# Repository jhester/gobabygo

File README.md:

GoBabyGo Project Repository
=====

This repo holds the firmware, software, hardware, and other files fort the GoBabyGo utilization project.

#### Visualize Data with Google Earth

Use the `create_nmea.py` script in the `analysis` folder to convert gathered GPS data into a single [NMEA file](https://www.gpsworld.com/what-exactly-is-gps-nmea-data/) which can be dragged into [Google Earth Pro (free)](https://www.google.com/earth/versions/#earth-pro), the desktop app.

To do this you need Python, once installed run the following in a command prompt or in a terminal where you specify the path to all the data and then specify the name of the NMEA file:

```
python create_nmea.py folder/where/files/are -o outputfile.nmea
```

If you import only tracks, it renders faster  but you dont get each value. If you import the LineStrings then it shows every value and also shows direction and time which is nice.

This could be trimmed down to show per day possibly.

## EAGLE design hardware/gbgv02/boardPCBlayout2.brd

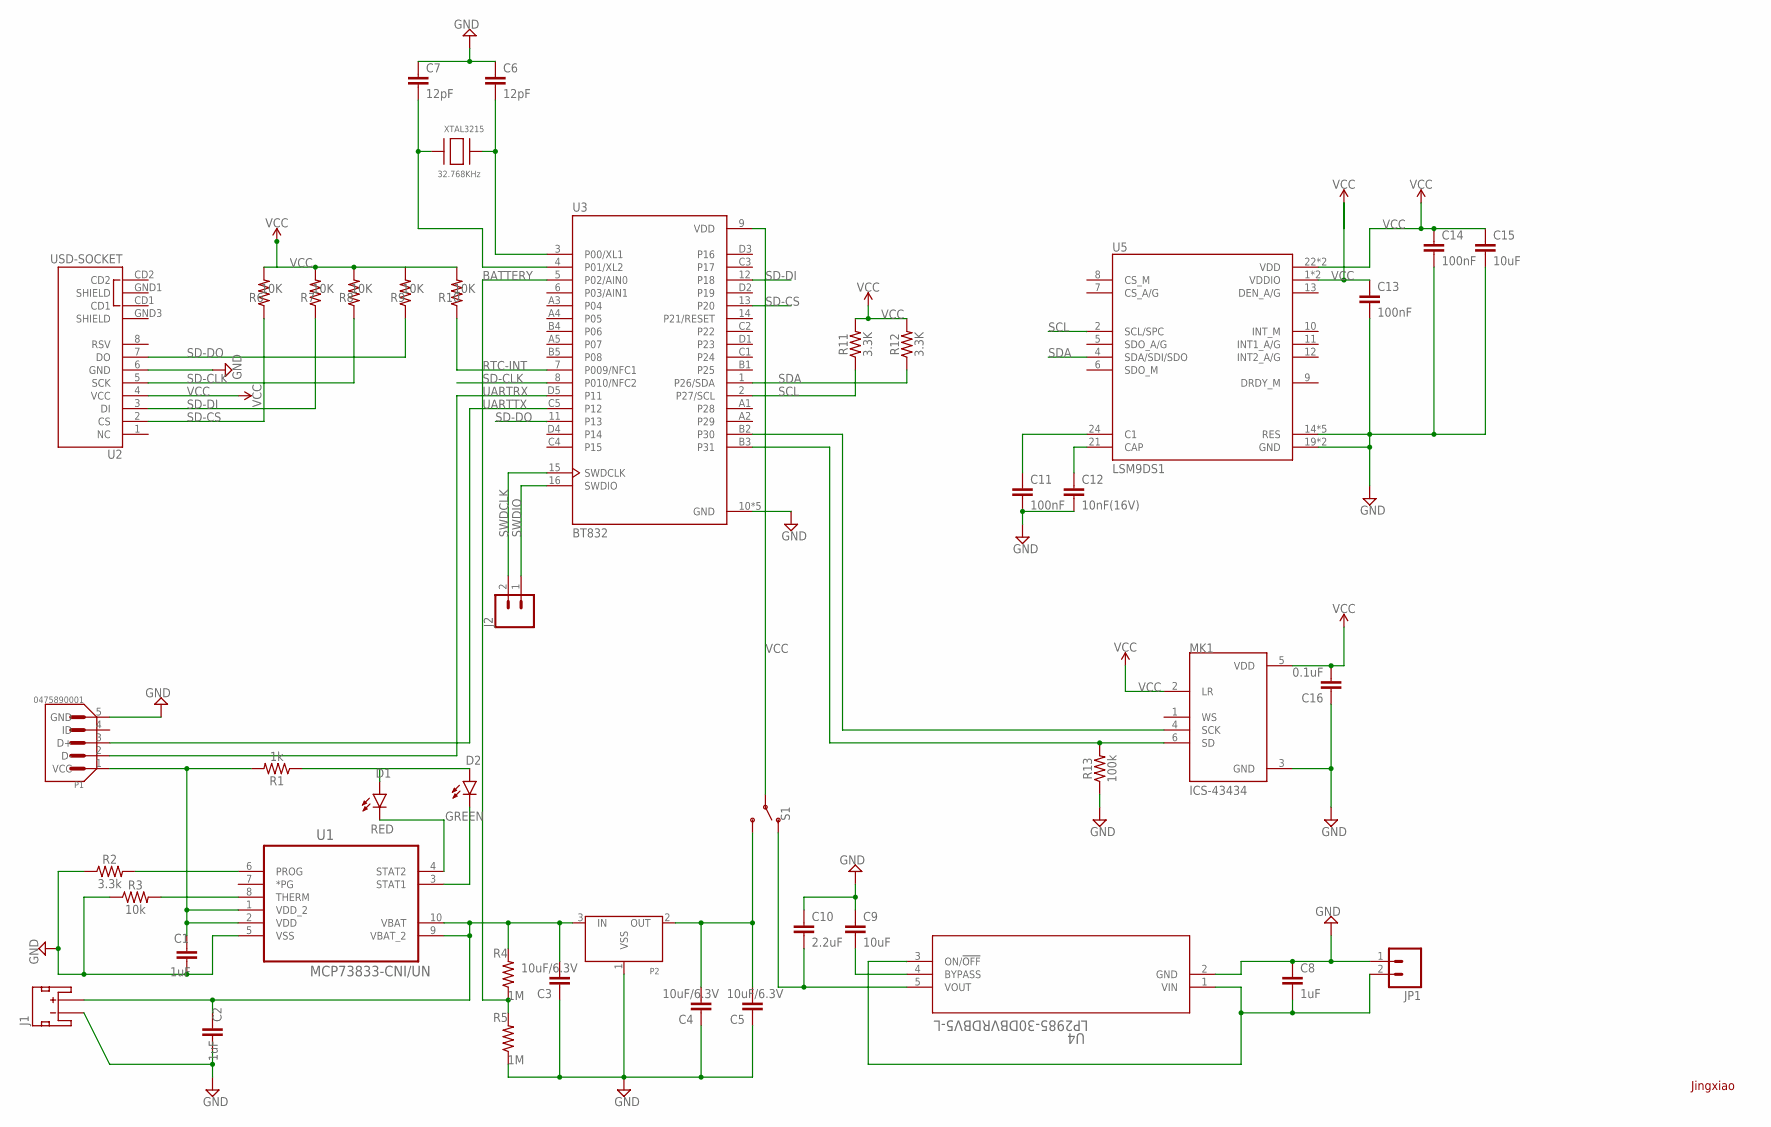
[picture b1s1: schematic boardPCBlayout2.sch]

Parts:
C1, C2: 1uF; CAP_0603
C3, C4, C5: 10uF/6.3V; 0603
C6, C7: 12pF; 0603
C8: 1uF; 0603
C9, C15: 10uF; 0603
C10: 2.2uF; 0603
C11, C13, C14: 100nF; 0603
C12: 10nF(16V); 0603
C16: 0.1uF; 0603
D1: RED; LED-0603
D2: GREEN; LED-0603
J1: JST_2MM_MALE; JST-2-SMD
J2: CONN_02; 1X02
JP1: M023.5MM-NO_SILK; SCREWTERMINAL-3.5MM-2-NS
MK1: ICS-43434; MIC_ICS-43434
P1: 0475890001; MOLEX_0475890001
P2: XC6206SOT-23; XC6206_SOT-23
R1: 1k; 0603
R2: 3.3k; 0603
R3: 10k; 0603
R4, R5: 1M; 0603
R6, R7, R8, R9, R10: 10K; 0603
R11, R12: 3.3K; 0603
R13: 100k; 0603
S1: SWITCH-SPDT-PTH-11.6X4.0MM; SWITCH_SPDT_PTH_11.6X4.0MM
U1: MCP73833-CNI/UN; SOP50P490X110-10N
U2: USD-SOCKET; MICROSD_1:1
U3: BT832; BLEMODULE_BT832
U4: LP2985-30DBVRDBV5-L; DBV5-L
U5: LSM9DS1; PQFN24P43_350X300X102L35X23N
XTAL3215: 32.768KHz; XTAL3215

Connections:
BATTERY: R4.1, R5.2, U3.5 (P02/AIN0)
GND: C1.2, C3.1, C4.1, C5.1, C6.1, C7.1, C8.1, C9.1, C10.1, C11.2, C12.2, C13.2, C14.2, C15.2, C16.1, JP1.1, MK1.3 (GND), P1.5 (GND), P2.1 (VSS), R2.1, R3.1, R5.1, R13.1, U1.5 (VSS), U2.6 (GND), U3.10 (GND), U3.A0 (GND), U3.B0 (GND), U3.C0 (GND), U3.D0 (GND), U4.2 (GND), U5.14 (RES), U5.15 (RES), U5.16 (RES), U5.17 (RES), U5.18 (RES), U5.19 (GND), U5.20 (GND)
unnamed: C1.1, P1.1 (VCC), R1.2, U1.1 (VDD_2), U1.2 (VDD)
unnamed: D1.C, U1.4 (STAT2)
unnamed: D1.A, D2.A, R1.1
unnamed: D2.C, U1.3 (STAT1)
unnamed: C2.2, J1.1 (-)
unnamed: C2.1, C3.2, J1.2 (+), P2.3 (IN), R4.2, U1.9 (VBAT_2), U1.10 (VBAT)
unnamed: R2.2, U1.6 (PROG)
unnamed: R3.2, U1.8 (THERM)
unnamed: MK1.6 (SD), R13.2, U3.B3 (P31)
unnamed: C7.2, U3.4 (P01/XL2), XTAL3215.P$1
unnamed: C6.2, U3.3 (P00/XL1), XTAL3215.P$2
unnamed: C10.2, S1.1 (O), U4.5 (VOUT)
unnamed: C12.1, U5.21 (CAP)
unnamed: C8.2, JP1.2, U4.1 (VIN), U4.3 (ON/!OFF)
unnamed: C9.2, U4.4 (BYPASS)
unnamed: C11.1, U5.24 (C1)
unnamed: C4.2, C5.2, P2.2 (OUT), S1.3 (S)
unnamed: MK1.4 (SCK), U3.B2 (P30)
RTC-INT: R10.1, U3.7 (P009/NFC1)
SCL: R11.1, U3.2 (P27/SCL), U5.2 (SCL/SPC)
SD-CLK: R8.1, U2.5 (SCK), U3.8 (P010/NFC2)
SD-CS: R6.1, U2.2 (CS), U3.13 (P20)
SD-DI: R7.1, U2.3 (DI), U3.12 (P18)
SD-DO: R9.1, U2.7 (DO), U3.11 (P13)
SDA: R12.1, U3.1 (P26/SDA), U5.4 (SDA/SDI/SDO)
SWDCLK: J2.2, U3.15 (SWDCLK)
SWDIO: J2.1, U3.16 (SWDIO)
UARTRX: P1.2 (D-), U3.D5 (P11)
UARTTX: P1.3 (D+), U3.C5 (P12)
VCC: C13.1, C14.1, C15.1, C16.2, MK1.2 (LR), MK1.5 (VDD), R6.2, R7.2, R8.2, R9.2, R10.2, R11.2, R12.2, S1.2, U2.4 (VCC), U3.9 (VDD), U5.1 (VDDIO), U5.3 (VDDIO), U5.22 (VDD), U5.23 (VDD)

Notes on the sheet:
Jingxiao

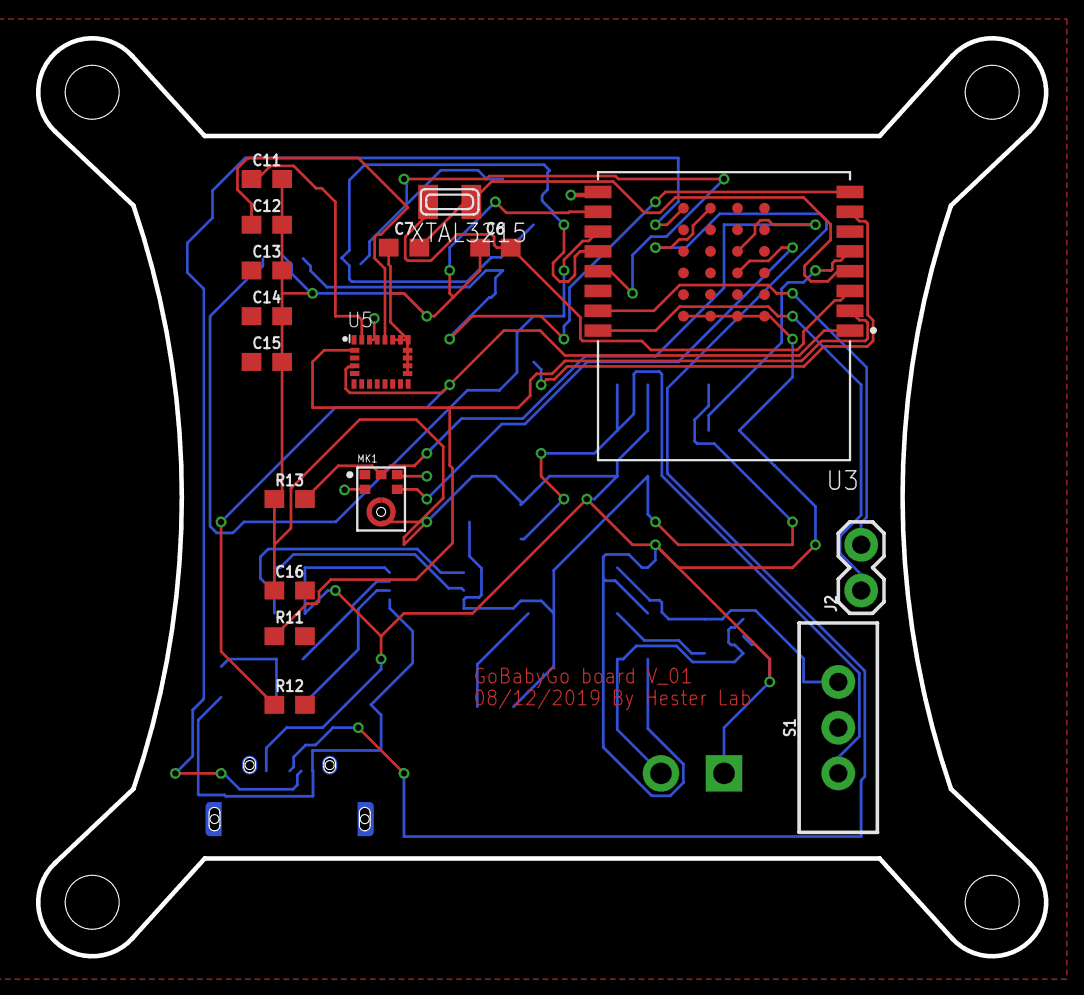
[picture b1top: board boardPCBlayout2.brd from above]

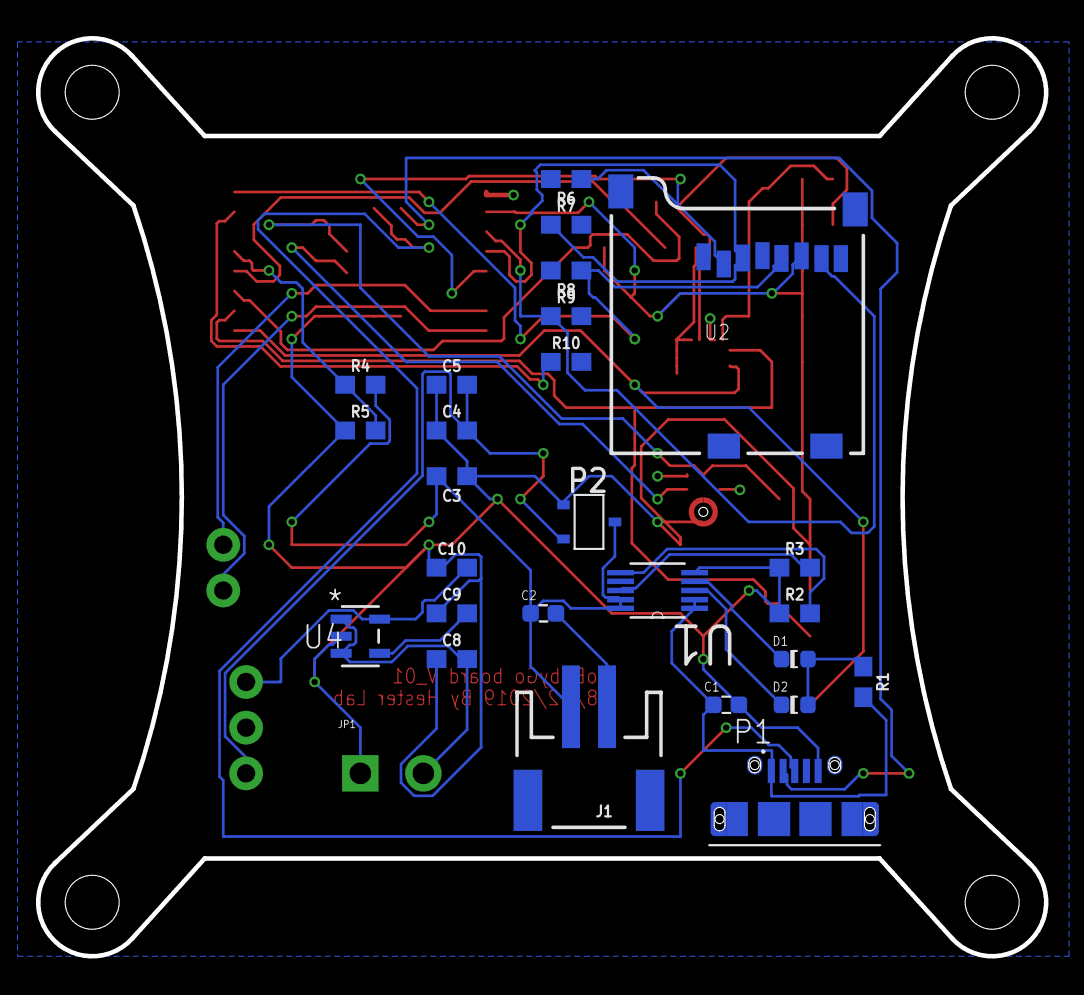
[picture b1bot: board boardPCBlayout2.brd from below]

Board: 2 copper layers, 56.0 x 51.0 mm, 44 parts (27 on the bottom side), 32 nets.

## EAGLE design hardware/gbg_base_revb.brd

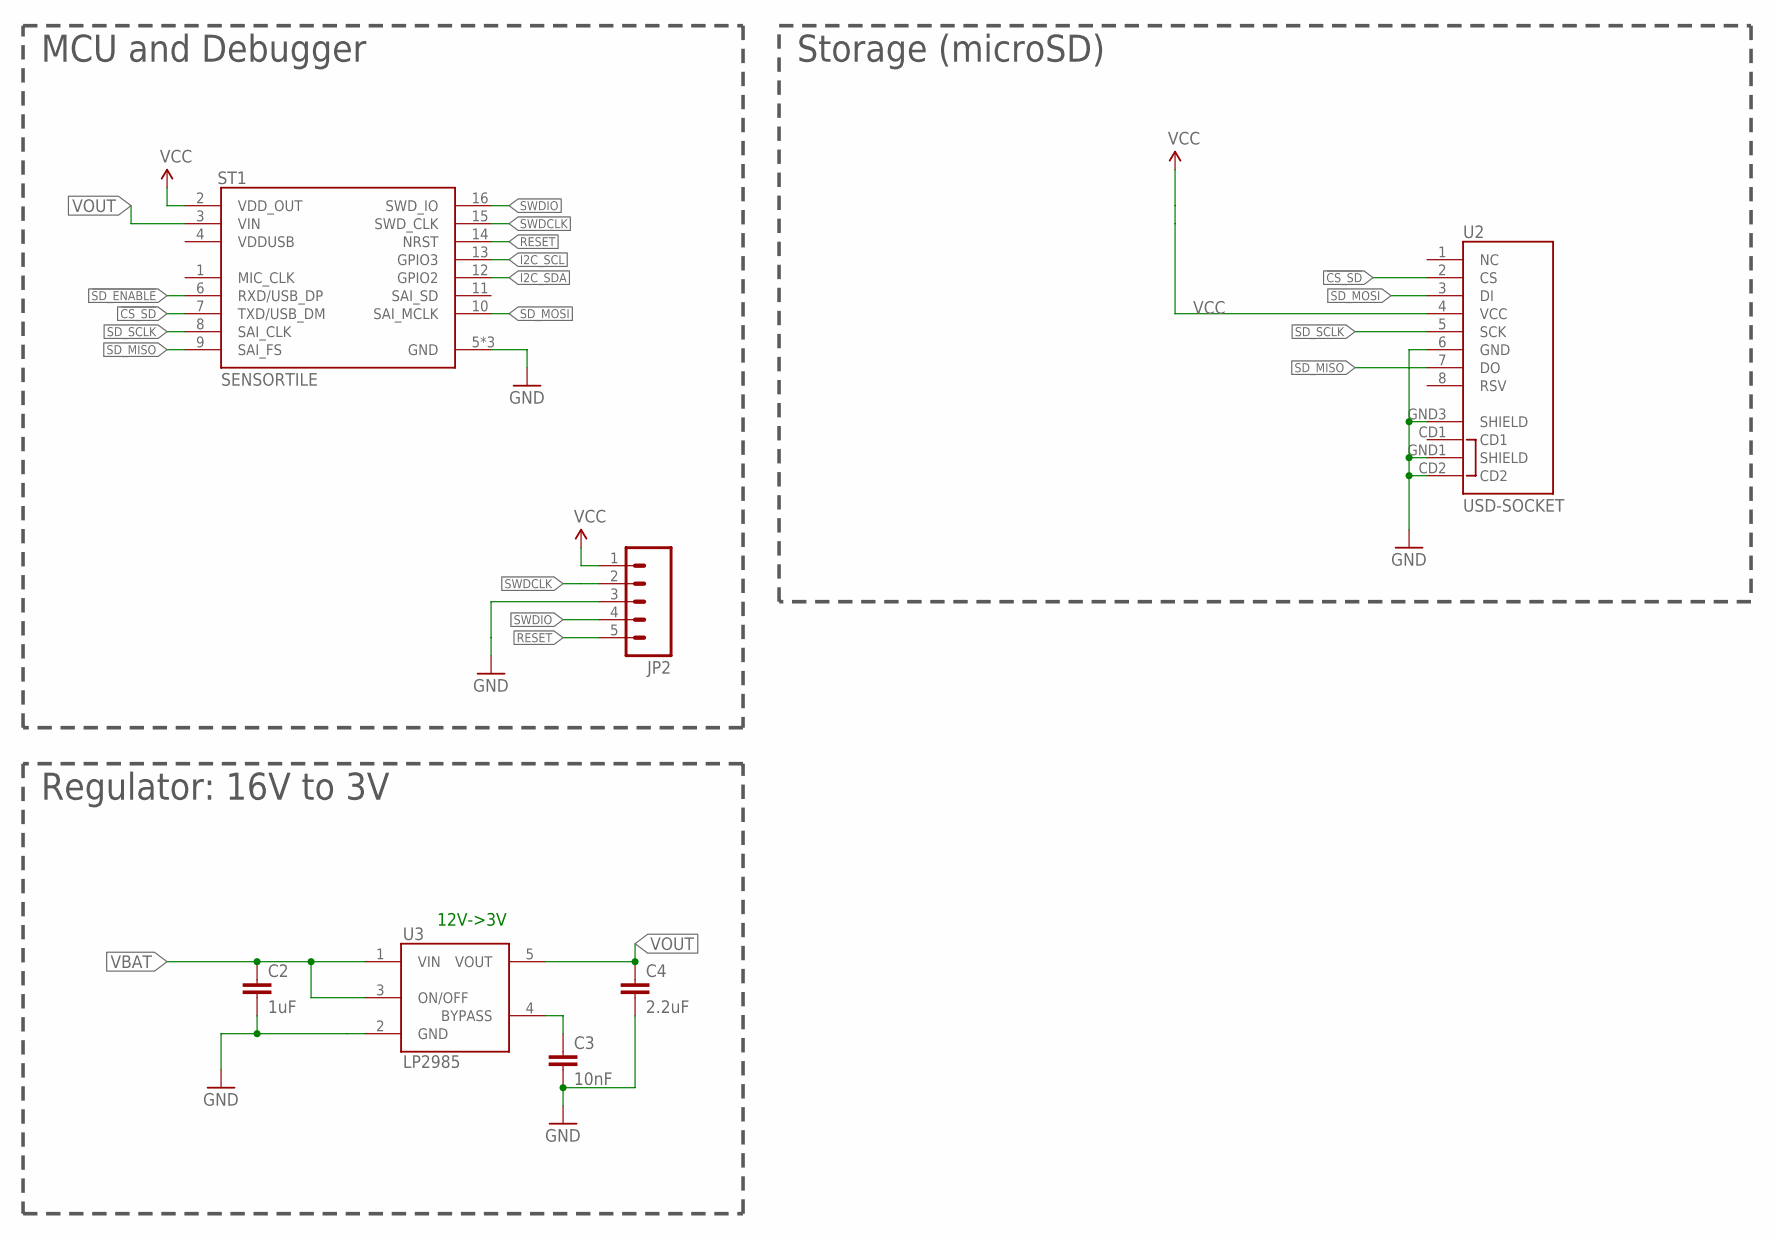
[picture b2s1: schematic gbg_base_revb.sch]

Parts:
C2: 1uF; 0603
C3: 10nF; 0603
C4: 2.2uF; 0603
JP2: M05LOCK; 1X05_LOCK
ST1: SENSORTILE
U2: USD-SOCKET; MICROSD_1:1; DIGIKEY WM3290CT-ND
U3: LP2985AIM5-3.3; SOT25; MPN LP2985-30DBVR; DIGIKEY 296-32152-1-ND

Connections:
!CS_SD: ST1.7 (TXD/USB_DM), U2.2 (CS)
!SD_ENABLE: ST1.6 (RXD/USB_DP)
BYPASS: C3.1, U3.4 (BYPASS)
GND: C2.2, C3.2, C4.2, JP2.3, ST1.5 (GND), ST1.17 (GND), ST1.18 (GND), U2.6 (GND), U2.CD2, U2.GND1 (SHIELD), U2.GND3 (SHIELD), U3.2 (GND)
I2C_SCL: ST1.13 (GPIO3)
I2C_SDA: ST1.12 (GPIO2)
RESET: JP2.5, ST1.14 (NRST)
SD_MISO: ST1.9 (SAI_FS), U2.7 (DO)
SD_MOSI: ST1.10 (SAI_MCLK), U2.3 (DI)
SD_SCLK: ST1.8 (SAI_CLK), U2.5 (SCK)
SWDCLK: JP2.2, ST1.15 (SWD_CLK)
SWDIO: JP2.4, ST1.16 (SWD_IO)
VBAT: C2.1, U3.1 (VIN), U3.3 (ON/OFF)
VCC: JP2.1, ST1.2 (VDD_OUT), U2.4 (VCC)
VOUT: C4.1, ST1.3 (VIN), U3.5 (VOUT)

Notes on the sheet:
Storage (microSD)
12V->3V
MCU and Debugger
Regulator: 16V to 3V

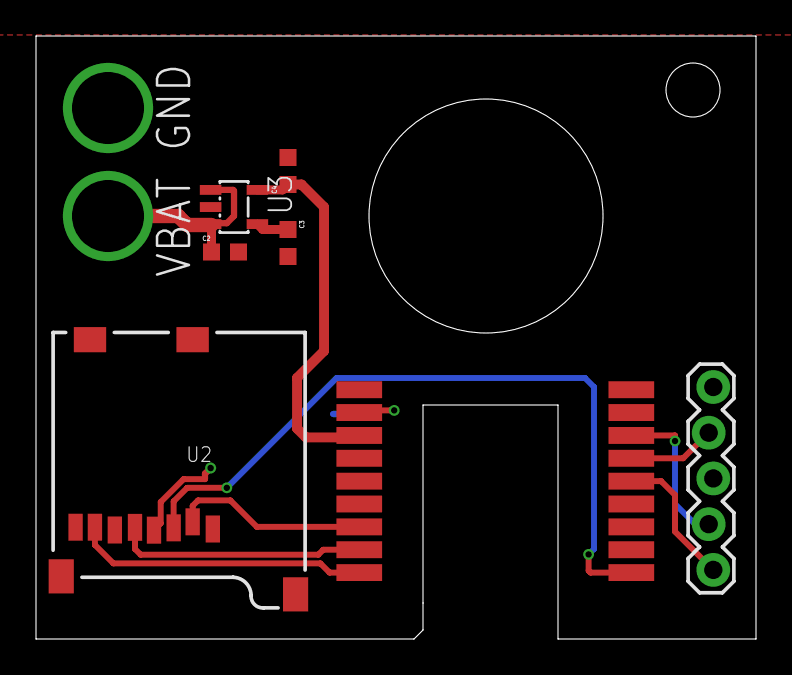
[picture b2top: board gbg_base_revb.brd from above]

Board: 2 copper layers, 40.0 x 33.5 mm, 7 parts (0 on the bottom side), 12 nets.

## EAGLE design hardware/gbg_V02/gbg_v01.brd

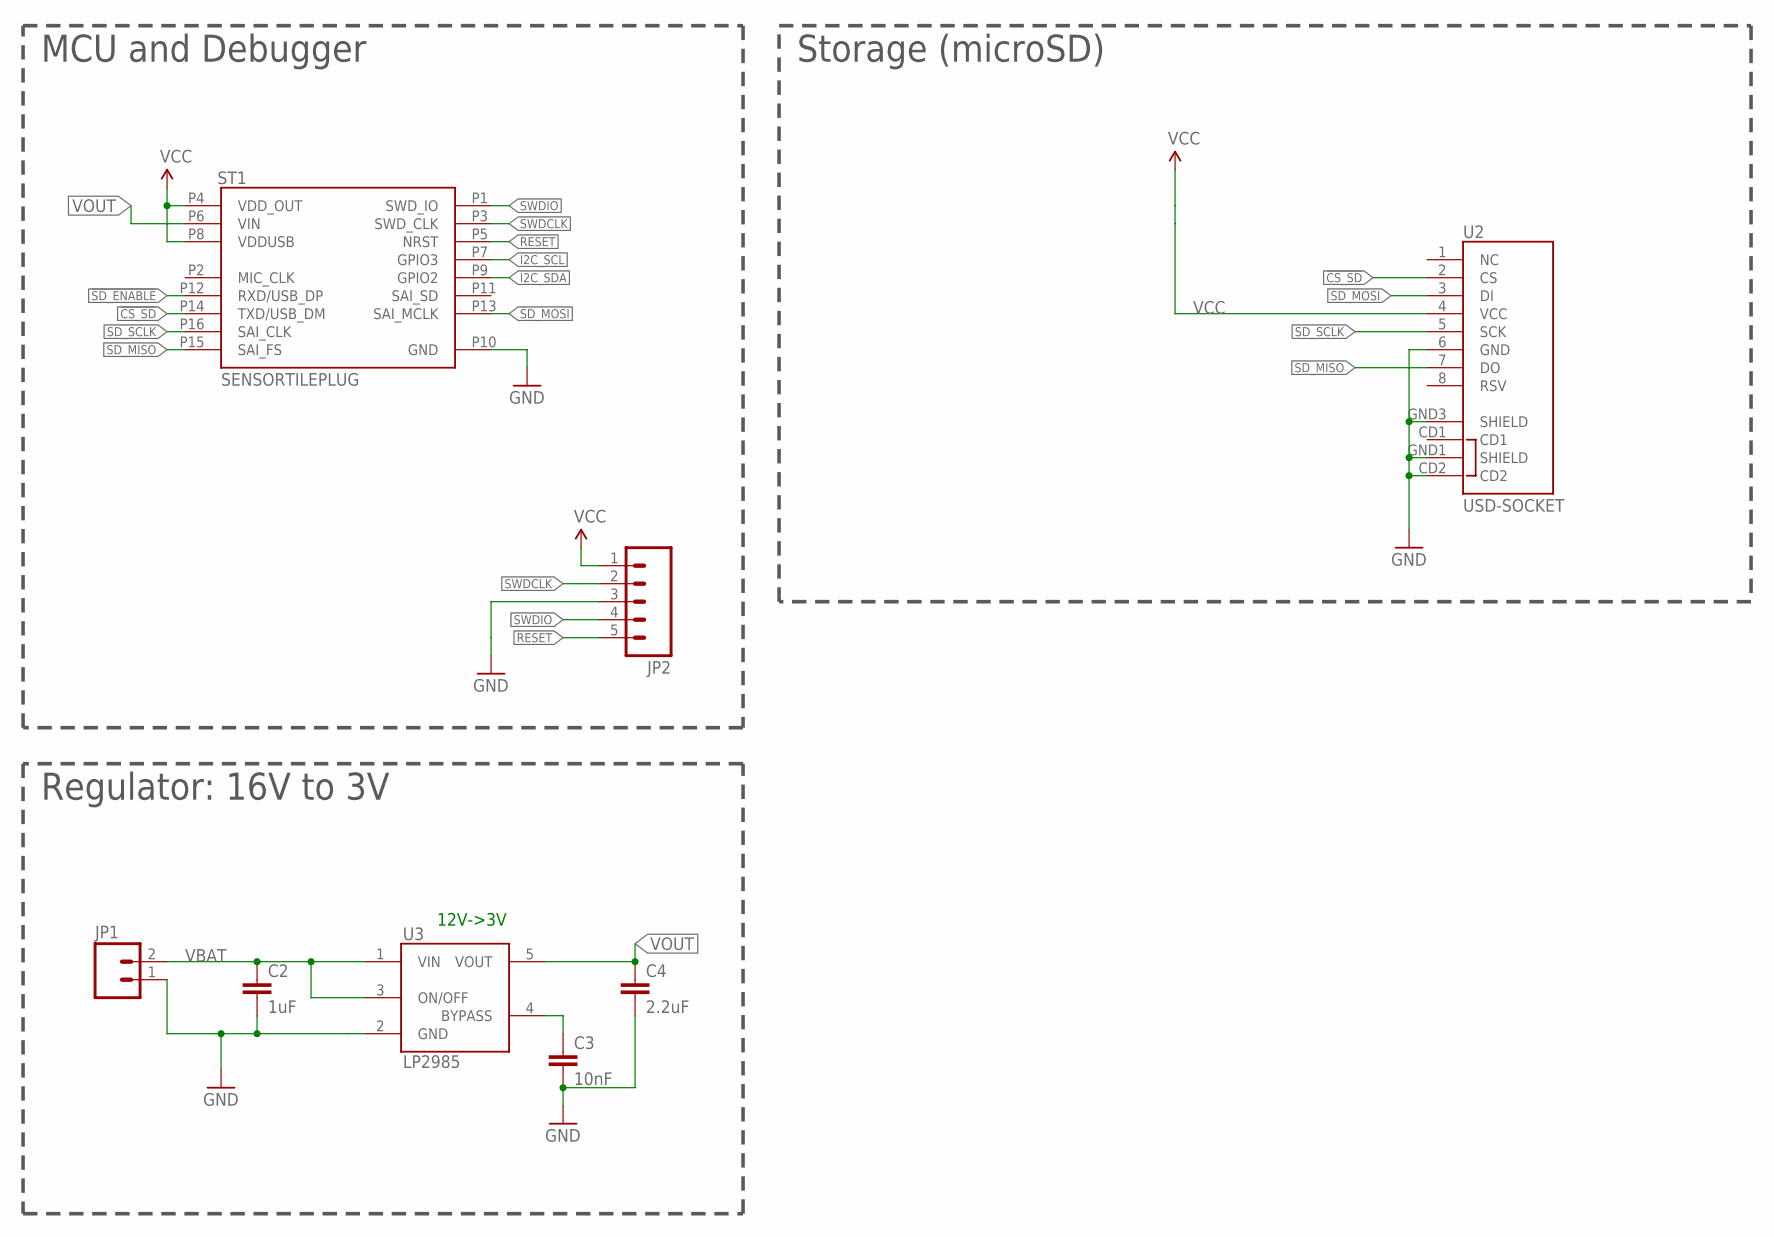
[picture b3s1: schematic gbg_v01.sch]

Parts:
C2: 1uF; 0603
C3: 10nF; 0603
C4: 2.2uF; 0603
JP1: M025MM; SCREWTERMINAL-5MM-2
JP2: M05LOCK; 1X05_LOCK
ST1: SENSORTILEPLUG; BM10JC16
U2: USD-SOCKET; MICROSD_1:1; DIGIKEY WM3290CT-ND
U3: LP2985AIM5-3.3; SOT25; MPN LP2985-30DBVR; DIGIKEY 296-32152-1-ND

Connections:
!CS_SD: ST1.P14 (TXD/USB_DM), U2.2 (CS)
!SD_ENABLE: ST1.P12 (RXD/USB_DP)
BYPASS: C3.1, U3.4 (BYPASS)
GND: C2.2, C3.2, C4.2, JP1.1, JP2.3, ST1.P10 (GND), U2.6 (GND), U2.CD2, U2.GND1 (SHIELD), U2.GND3 (SHIELD), U3.2 (GND)
I2C_SCL: ST1.P7 (GPIO3)
I2C_SDA: ST1.P9 (GPIO2)
RESET: JP2.5, ST1.P5 (NRST)
SD_MISO: ST1.P15 (SAI_FS), U2.7 (DO)
SD_MOSI: ST1.P13 (SAI_MCLK), U2.3 (DI)
SD_SCLK: ST1.P16 (SAI_CLK), U2.5 (SCK)
SWDCLK: JP2.2, ST1.P3 (SWD_CLK)
SWDIO: JP2.4, ST1.P1 (SWD_IO)
VBAT: C2.1, JP1.2, U3.1 (VIN), U3.3 (ON/OFF)
VCC: JP2.1, ST1.P4 (VDD_OUT), ST1.P8 (VDDUSB), U2.4 (VCC)
VOUT: C4.1, ST1.P6 (VIN), U3.5 (VOUT)

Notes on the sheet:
Storage (microSD)
12V->3V
MCU and Debugger
Regulator: 16V to 3V

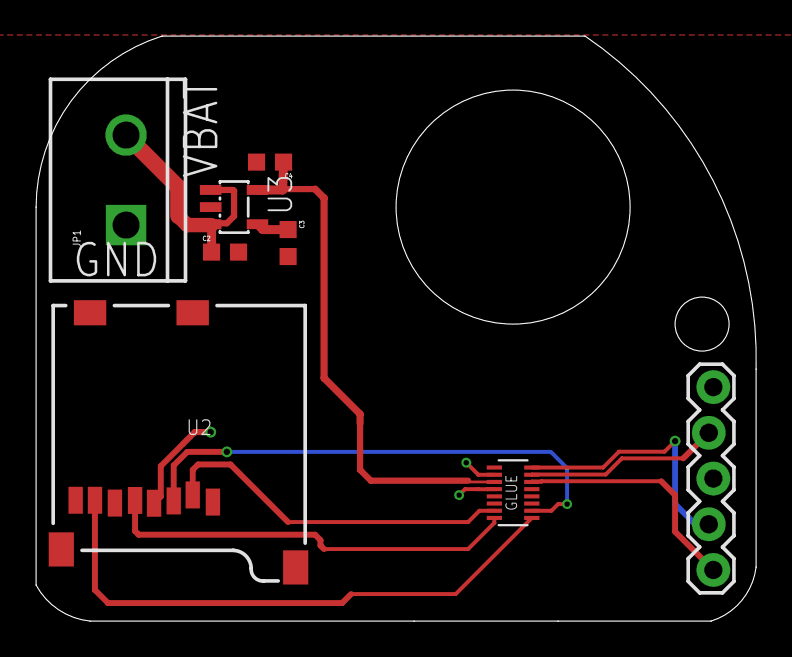
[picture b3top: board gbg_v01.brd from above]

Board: 2 copper layers, 40.0 x 32.5 mm, 8 parts (0 on the bottom side), 12 nets.

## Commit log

2019-05-30 fixed bug, LED blink not implement
2019-05-31 improve save file parts
2019-06-06 sample in 10Hz, write every 10-14 rows
2019-06-11 tickless sleep mode
2019-06-13 fix timestamp
2019-07-07 Update structure, add hardware files
2019-07-07 added readme
2019-07-09 new hardware, simple
2019-07-25 Create CAD
2019-08-08 Create 1
2019-08-13 Create 11
2019-08-14 visualization, basic calculation on location and distance
2019-08-15 polygons
2019-08-16 add turns
2019-08-21 Utilize magneto for direction
2019-10-05 added new esp32 arduino firmware
2019-10-05 removed extras
2020-03-25 moved things around, added script for google earth viz

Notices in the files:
parts and their libraries:
SparkFun-Aesthetics: Licensing: Creative Commons ShareAlike 4.0 International - https://creativecommons.org/licenses/by-sa/4.0
